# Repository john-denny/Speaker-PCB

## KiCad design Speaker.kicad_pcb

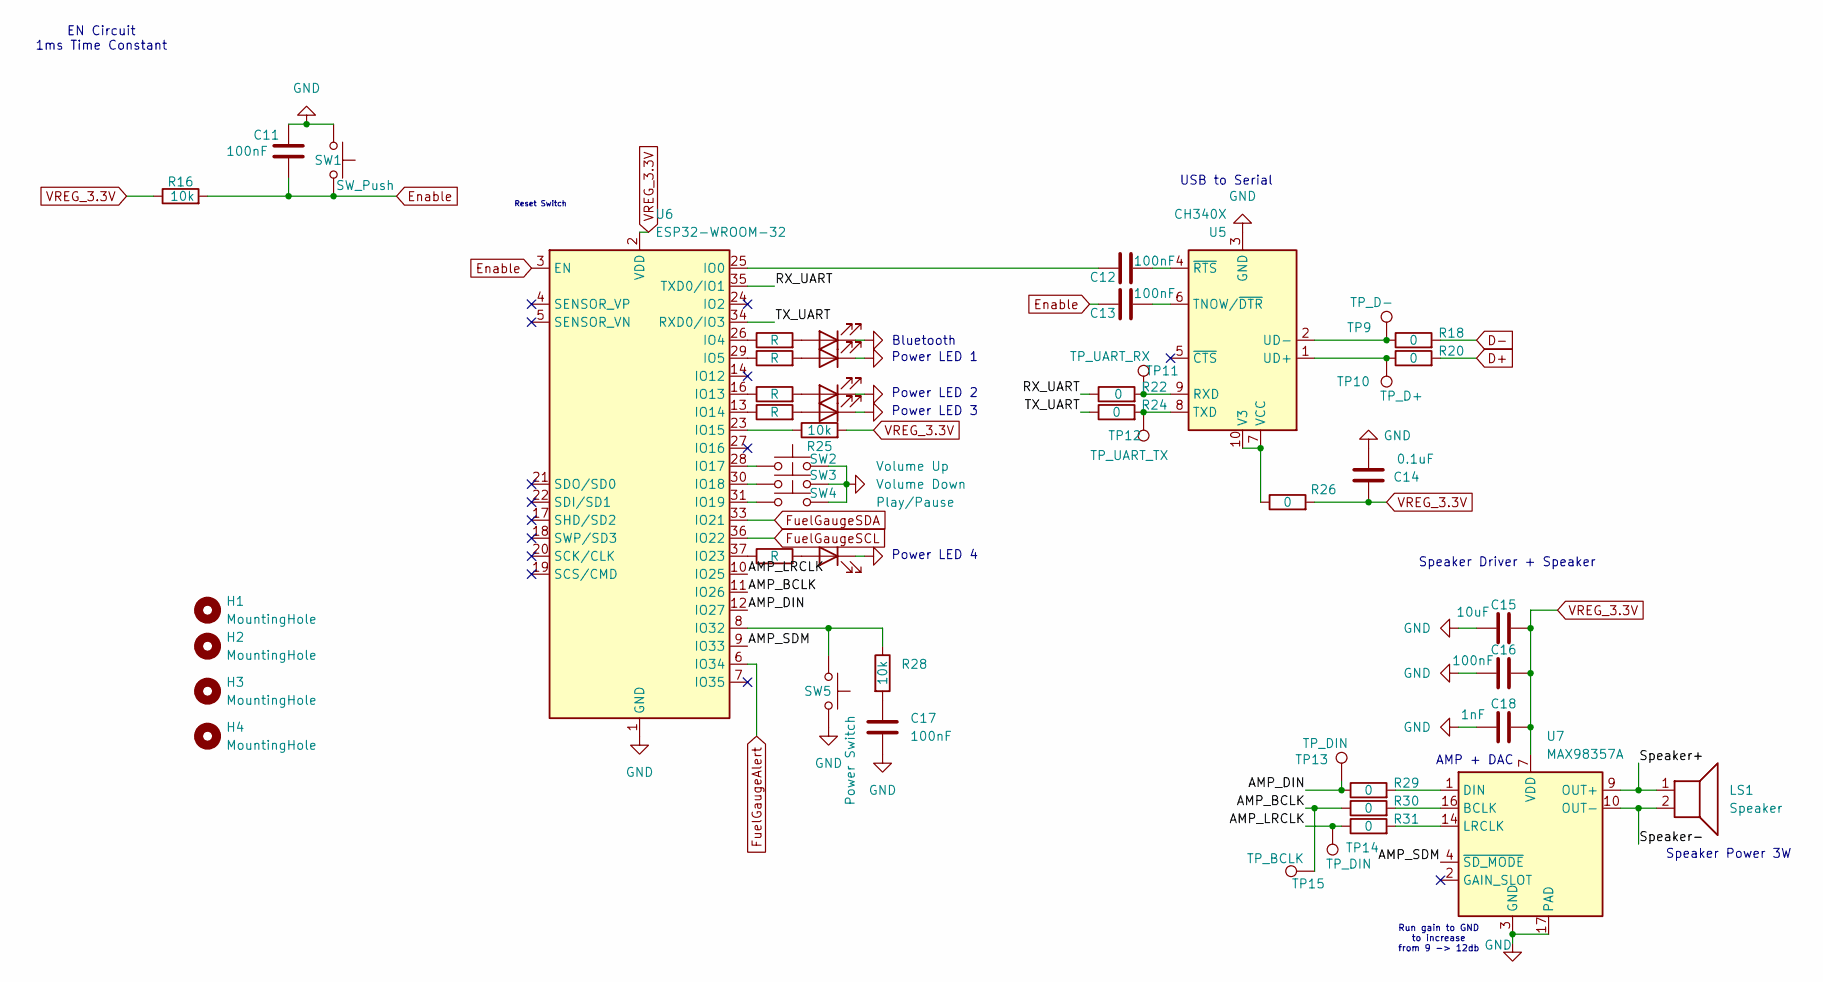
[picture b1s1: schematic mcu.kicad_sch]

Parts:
C11, C12, C13, C16, C17: 100nF; C_0603_1608Metric_Pad1.08x0.95mm_HandSolder
C14: 0.1uF; C_0603_1608Metric_Pad1.08x0.95mm_HandSolder
C15: 10uF; C_0603_1608Metric_Pad1.08x0.95mm_HandSolder
C18: 1nF; C_0603_1608Metric_Pad1.08x0.95mm_HandSolder
D3, D4, D5, D6, D7: LED; LED_0603_1608Metric_Pad1.05x0.95mm_HandSolder
H1, H2, H3, H4: MountingHole; MountingHole_2.2mm_M2_Pad_Via
LS1: Speaker; JST_PH_S2B-PH-K_1x02_P2.00mm_Horizontal
R16, R25, R28: 10k; R_0603_1608Metric_Pad0.98x0.95mm_HandSolder
R17, R19, R21, R23, R27: R; R_0603_1608Metric_Pad0.98x0.95mm_HandSolder
R18, R20, R22, R24, R26, R29, R30, R31: 0; R_0603_1608Metric_Pad0.98x0.95mm_HandSolder
SW1: SW_Push; SW_SPST_B3U-1000P
SW2: Volume Up; SW_SPST_B3U-1000P
SW3: Volume Down; SW_SPST_B3U-1000P
SW4: Play/Pause; SW_SPST_B3U-1000P
SW5: Power Switch; SW_SPST_B3U-1000P
TP9: TP_D-; TestPoint_Pad_D1.5mm
TP10: TP_D+; TestPoint_Pad_D1.5mm
TP11: TP_UART_RX; TestPoint_Pad_D1.5mm
TP12: TP_UART_TX; TestPoint_Pad_D1.5mm
TP13, TP14: TP_DIN; TestPoint_Pad_D1.5mm
TP15: TP_BCLK; TestPoint_Pad_D1.5mm
U5: CH340X; MSOP-10_3x3mm_P0.5mm
U6: ESP32-WROOM-32
U7: MAX98357A; TQFN-16-1EP_3x3mm_P0.5mm_EP1.23x1.23mm

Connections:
/MCU/AMP_BCLK: R30.1, TP15.1, U6.11 (IO26)
/MCU/AMP_DIN: R29.1, TP13.1, U6.12 (IO27)
/MCU/AMP_LRCLK: R31.1, TP14.1, U6.10 (IO25)
/MCU/AMP_SDM: U6.9 (IO33), U7.4 (~SD_MODE)
/MCU/RX_UART: R22.1, U6.35 (TXD0/IO1)
/MCU/Speaker+: LS1.1, U7.9 (OUT+)
/MCU/Speaker-: LS1.2, U7.10 (OUT-)
/MCU/TX_UART: R24.1, U6.34 (RXD0/IO3)
D+: R20.2; also elsewhere on the board
D-: R18.2; also elsewhere on the board
Enable: C11.2, C13.1, R16.2, SW1.2, U6.3 (EN)
FuelGaugeAlert: U6.6 (IO34); also elsewhere on the board
FuelGaugeSCL: U6.36 (IO22); also elsewhere on the board
FuelGaugeSDA: U6.33 (IO21); also elsewhere on the board
GND: C11.1, C14.1, C15.1, C16.1, C17.2, C18.1, D3.1 (K), D4.1 (K), D5.1 (K), D6.1 (K), D7.1 (K), SW1.1, SW2.2, SW3.2, SW4.2, SW5.2, U5.3 (GND), U6.1 (GND), U6.15 (GND), U6.38 (GND), U6.39 (GND), U7.3 (GND), U7.11 (GND), U7.15 (GND), U7.17 (PAD); also elsewhere on the board
unnamed: C17.1, R28.2
unnamed: D3.2 (A), R17.2
unnamed: D4.2 (A), R19.2
unnamed: D5.2 (A), R21.2
unnamed: D6.2 (A), R23.2
unnamed: D7.2 (A), R27.2
unnamed: R22.2, TP11.1, U5.9 (RXD)
unnamed: C13.2, U5.6 (TNOW/~DTR)
unnamed: R24.2, TP12.1, U5.8 (TXD)
unnamed: R20.1, TP10.1, U5.1 (UD+)
unnamed: R18.1, TP9.1, U5.2 (UD-)
unnamed: R26.1, U5.7 (VCC), U5.10 (V3)
unnamed: C12.2, U5.4 (~RTS)
unnamed: C12.1, U6.25 (IO0)
unnamed: R17.1, U6.26 (IO4)
unnamed: R19.1, U6.29 (IO5)
unnamed: R21.1, U6.16 (IO13)
unnamed: R23.1, U6.13 (IO14)
unnamed: R25.1, U6.23 (IO15)
unnamed: SW2.1, U6.28 (IO17)
unnamed: SW3.1, U6.30 (IO18)
unnamed: SW4.1, U6.31 (IO19)
unnamed: R27.1, U6.37 (IO23)
unnamed: R28.1, SW5.1, U6.8 (IO32)
unnamed: R30.2, U7.16 (BCLK)
unnamed: R29.2, U7.1 (DIN)
unnamed: R31.2, U7.14 (LRCLK)
VREG_3.3V: C14.2, C15.2, C16.2, C18.2, R16.1, R25.2, R26.2, U6.2 (VDD), U7.7 (VDD), U7.8 (VDD); also elsewhere on the board

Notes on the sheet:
AMP + DAC
Reset Switch
Power LED 4
Bluetooth
EN Circuit 1ms Time Constant
Speaker Driver + Speaker
Power LED 3
USB to Serial
Speaker Power 3W
Run gain to GND to increase from 9 -> 12db
Power LED 2
Power LED 1

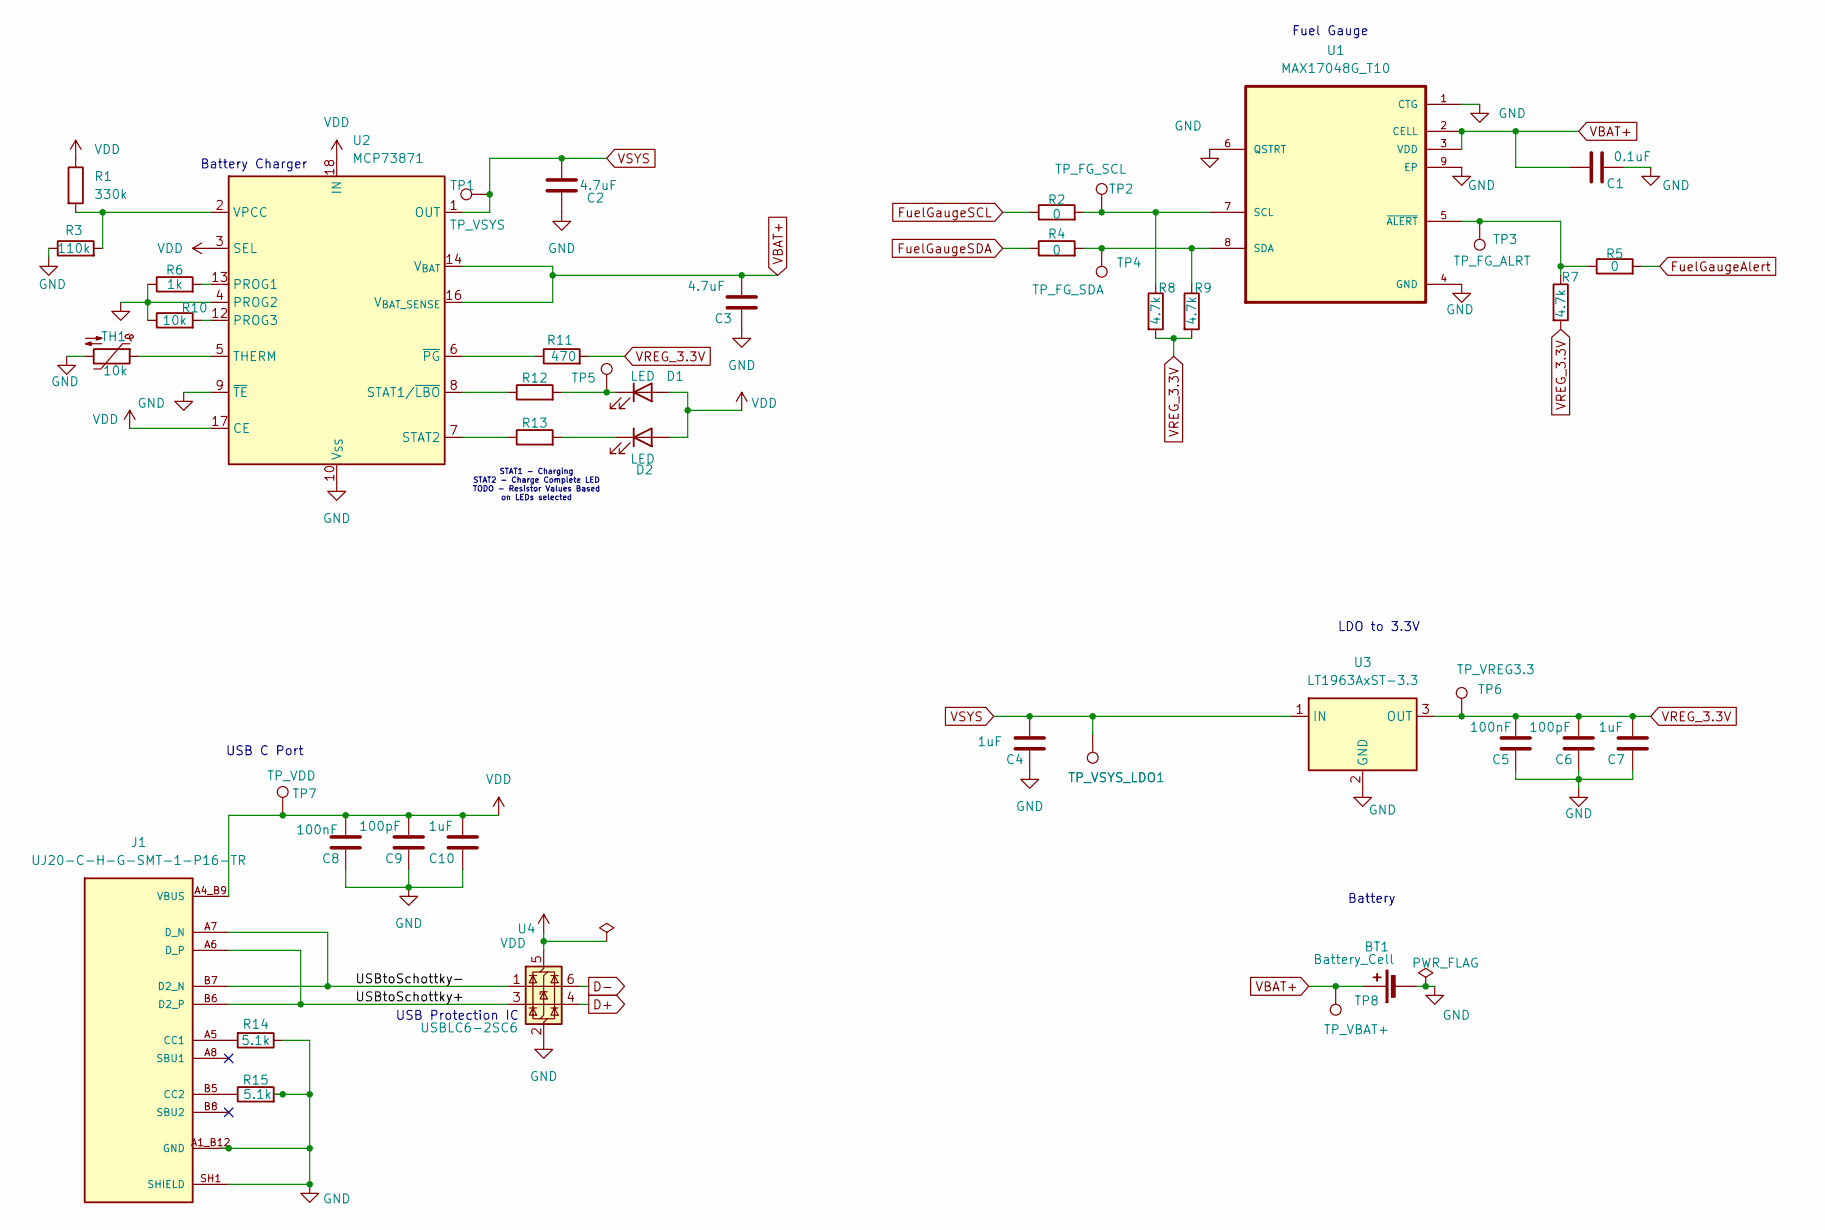
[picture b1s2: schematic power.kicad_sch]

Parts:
BT1: Battery_Cell; JST_PH_S2B-PH-K_1x02_P2.00mm_Horizontal
C1: 0.1uF; C_0603_1608Metric_Pad1.08x0.95mm_HandSolder
C2, C3: 4.7uF; C_0603_1608Metric_Pad1.08x0.95mm_HandSolder
C4, C7, C10: 1uF; C_0603_1608Metric_Pad1.08x0.95mm_HandSolder
C5, C8: 100nF; C_0603_1608Metric_Pad1.08x0.95mm_HandSolder
C6, C9: 100pF; C_0603_1608Metric_Pad1.08x0.95mm_HandSolder
D1, D2: LED; LED_0603_1608Metric_Pad1.05x0.95mm_HandSolder
J1: UJ20-C-H-G-SMT-1-P16-TR; SAMESKY_UJ20-C-H-G-SMT-1-P16-TR; PARTREV 1.0
R1: 330k; R_0603_1608Metric_Pad0.98x0.95mm_HandSolder
R2, R4, R5: 0; R_0603_1608Metric_Pad0.98x0.95mm_HandSolder
R3: 110k; R_0603_1608Metric_Pad0.98x0.95mm_HandSolder
R6: 1k; R_0603_1608Metric_Pad0.98x0.95mm_HandSolder
R7, R8, R9: 4.7k; R_0603_1608Metric_Pad0.98x0.95mm_HandSolder
R10: 10k; R_0603_1608Metric_Pad0.98x0.95mm_HandSolder
R11: 470; R_0603_1608Metric_Pad0.98x0.95mm_HandSolder
R12, R13: R_0603_1608Metric_Pad0.98x0.95mm_HandSolder
R14, R15: 5.1k; R_0603_1608Metric_Pad0.98x0.95mm_HandSolder
TH1: 10k; R_0603_1608Metric_Pad0.98x0.95mm_HandSolder
TP1: TP_VSYS; TestPoint_Pad_D1.5mm
TP2: TP_FG_SCL; TestPoint_Pad_D1.5mm
TP3: TP_FG_ALRT; TestPoint_Pad_D1.5mm
TP4: TP_FG_SDA; TestPoint_Pad_D1.5mm
TP5: TP_Charging; TestPoint_Pad_D1.5mm
TP6: TP_VREG3.3; TestPoint_Pad_D1.5mm
TP7: TP_VDD; TestPoint_Pad_D1.5mm
TP8: TP_VBAT+; TestPoint_Pad_D1.5mm
TP_VSYS_LDO1: TP_VSYS_LDO; TestPoint_Pad_D1.5mm
U1: MAX17048G_T10; SON50P200X200X80-9N
U2: MCP73871; QFN-20-1EP_4x4mm_P0.5mm_EP2.5x2.5mm
U3: LT1963AxST-3.3; SOT-223-3_TabPin2
U4: USBLC6-2SC6; SOT-23-6

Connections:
/Power/USBtoSchottky+: J1.A6 (D_P), J1.B6 (D2_P), U4.3 (I/O2)
/Power/USBtoSchottky-: J1.A7 (D_N), J1.B7 (D2_N), U4.1 (I/O1)
D+: U4.4 (I/O2); also elsewhere on the board
D-: U4.6 (I/O1); also elsewhere on the board
FuelGaugeAlert: R5.2; also elsewhere on the board
FuelGaugeSCL: R2.1; also elsewhere on the board
FuelGaugeSDA: R4.1; also elsewhere on the board
GND: BT1.2 (-), C1.2, C2.2, C3.2, C4.1, C5.1, C6.1, C7.1, C8.1, C9.1, C10.1, J1.A1_B12 (GND), J1.B1_A12 (GND), J1.SH1 (SHIELD), J1.SH2 (SHIELD), J1.SH3 (SHIELD), J1.SH4 (SHIELD), R3.1, R6.1, R10.1, R14.1, R15.2, TH1.2, U1.1 (CTG), U1.4 (GND), U1.6 (QSTRT), U1.9 (EP), U2.4 (PROG2), U2.9 (~TE), U2.10 (V_{SS}), U2.11 (V_{SS}), U2.21 (V_{SS}), U3.2 (GND), U4.2 (GND); also elsewhere on the board
unnamed: D1.1 (K), R12.2, TP5.1
unnamed: D2.1 (K), R13.2
unnamed: J1.A5 (CC1), R14.2
unnamed: J1.B5 (CC2), R15.1
unnamed: R2.2, R8.1, TP2.1, U1.7 (SCL)
unnamed: R4.2, R9.1, TP4.1, U1.8 (SDA)
unnamed: R5.1, R7.1, TP3.1, U1.5 (~ALERT)
unnamed: R6.2, U2.13 (PROG1)
unnamed: R10.2, U2.12 (PROG3)
unnamed: R12.1, U2.8 (STAT1/~LBO)
unnamed: R13.1, U2.7 (STAT2)
unnamed: TH1.1, U2.5 (THERM)
unnamed: R1.2, R3.2, U2.2 (VPCC)
unnamed: R11.1, U2.6 (~PG)
VBAT+: BT1.1 (+), C1.1, C3.1, TP8.1, U1.2 (CELL), U1.3 (VDD), U2.14 (V_{BAT}), U2.15 (V_{BAT}), U2.16 (V_{BAT_SENSE})
VDD: C8.2, C9.2, C10.2, D1.2 (A), D2.2 (A), J1.A4_B9 (VBUS), J1.B4_A9 (VBUS), R1.1, TP7.1, U2.3 (SEL), U2.17 (CE), U2.18 (IN), U2.19 (IN), U4.5 (VBUS)
VREG_3.3V: C5.2, C6.2, C7.2, R7.2, R8.2, R9.2, R11.2, TP6.1, U3.3 (OUT); also elsewhere on the board
VSYS: C2.1, C4.2, TP1.1, TP_VSYS_LDO1.1, U2.1 (OUT), U2.20 (OUT), U3.1 (IN)

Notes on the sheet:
LDO to 3.3V
Battery
USB C Port
USB Protection IC
Battery Charger
Fuel Gauge
STAT1 - Charging STAT2 - Charge Complete LED TODO - Resistor Values Based on LEDs selected

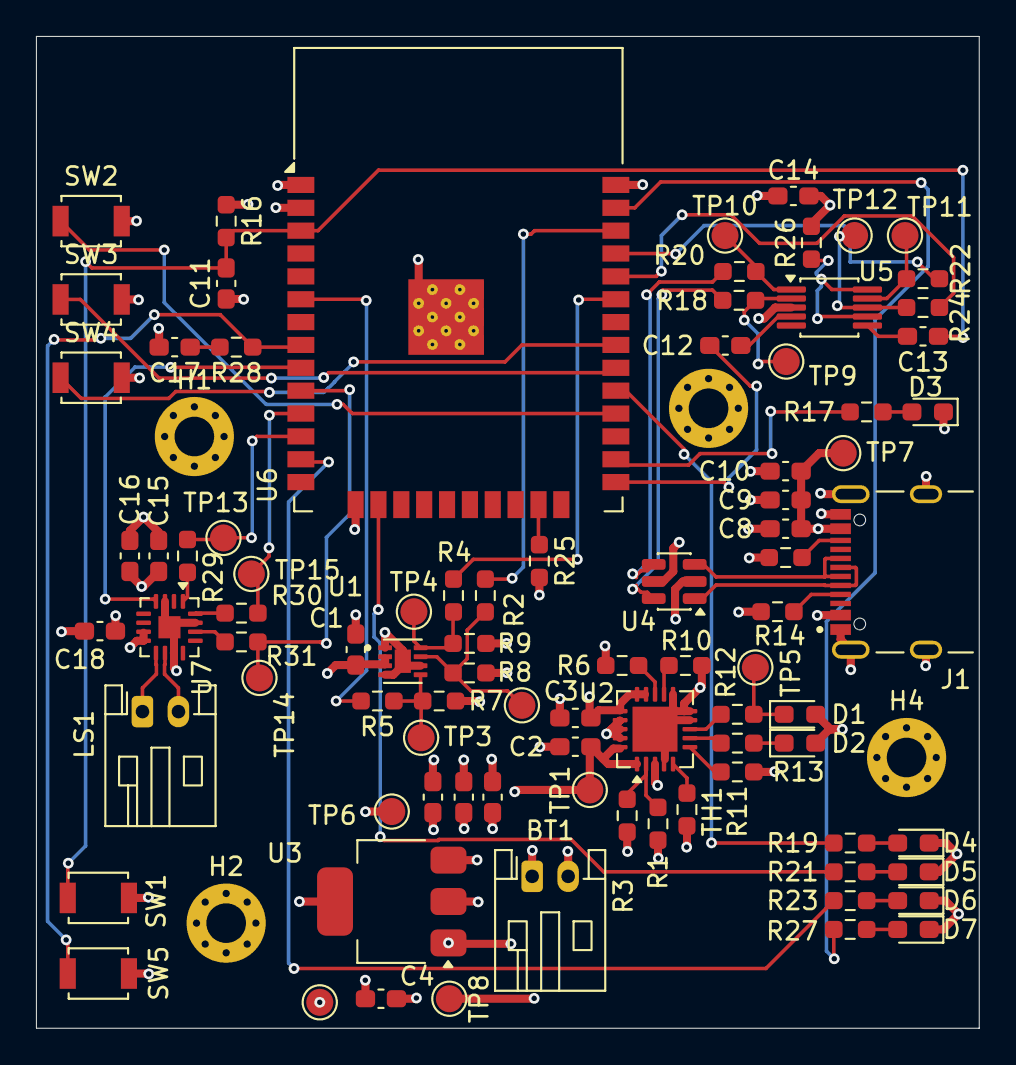
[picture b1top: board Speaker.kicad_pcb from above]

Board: 4 copper layers, 52.4 x 55.1 mm, 92 parts (0 on the bottom side), 62 nets.
